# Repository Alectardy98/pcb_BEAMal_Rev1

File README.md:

# BEAMAL Rev. 1 
    A Custom Replacment PCB and case, using the IBM 6580 Displaywriter System as a base

All Supported Layouts can be seen [HERE](http://www.keyboard-layout-editor.com/#/gists/b96d65da63be744e5e54532b00e9445a)

xwhatsit/QMK atmega32u4 pcb for the IBM Model F XT and IBM Bigfoot

This version has NOT YET been tested, THIS IS A SMALL PRODUCTION OF 5 UNITS, NEVER TO BE SOLD AGAIN
- The firmware can be found in the firmware folder
- All files for production though JLCPCB can be found in the JLCPCB folder
- This pcb requires an xwhatsit to function, see [purdeaandrei's open source files](https://github.com/purdeaandrei/SMDModelFController)
- Note, even though this is a beamspring pcb, it will use a model F xWhatsit replacment controller
- Test Points are currently on the pcb, when building make sure to cover the bottom test points with eletrical tape to prevent a short
- The barrel Plate will need to be modified, A replacment barrel plate file will be provided with the custom case files

The PCB thickness should be 0.6mm or 0.08mm. This is thin enough to allow the board to flex into shape.
- 0.8mm tested and working

Standard glossy soldermask is probably the best choice. JLCPCB has had issues with wear on their black soldermask before. They have changed the formula, but a standard green/red/blue/yellow/purple/white/etc. glossy solder mask is probaby the safest bet for keyswitch wear resistance. Higher wear resistance might also be achieved by coating the front of the capacitive pads in silkscreen, as silkscreen is an extra layer of epoxy. I am unsure how this will affect keyfeel or actuation, however.

For connecting the board to an xwhatsit or other controller, I would recommend [3M 8132/06 100](https://www.digikey.com/en/products/detail/3m/8132-06-100/7809902), which has the correct pitch to connect this pcb to an xwhatsit

Capacitive pad footprints have been created spificly for this project, as the White whale beamspring has an off axis footprint aligment. In order to stay true to the origional desigen philosphy, that change has been made here also. Thank you to  All mesurements have beeen take from an origonal IBM Displaywrighter system (BAE). The key matrix of the PCB is custom, made by myself, guided purdeaandrei.

Released without warranty, use at your own risk.  
PRs & feedback welcome!

| Authors | 

Alectardy98

| Special Thanks |
   
purdeaandrei - For many things, this project would not have happened without him.

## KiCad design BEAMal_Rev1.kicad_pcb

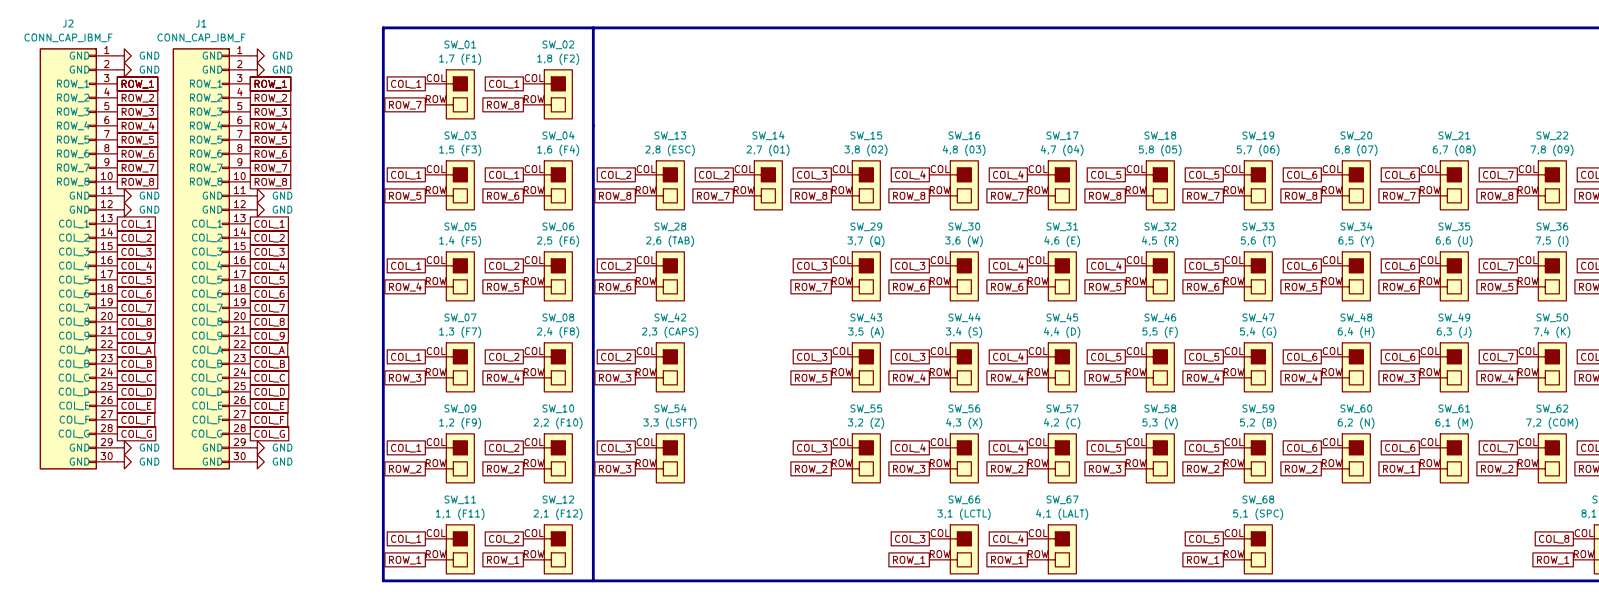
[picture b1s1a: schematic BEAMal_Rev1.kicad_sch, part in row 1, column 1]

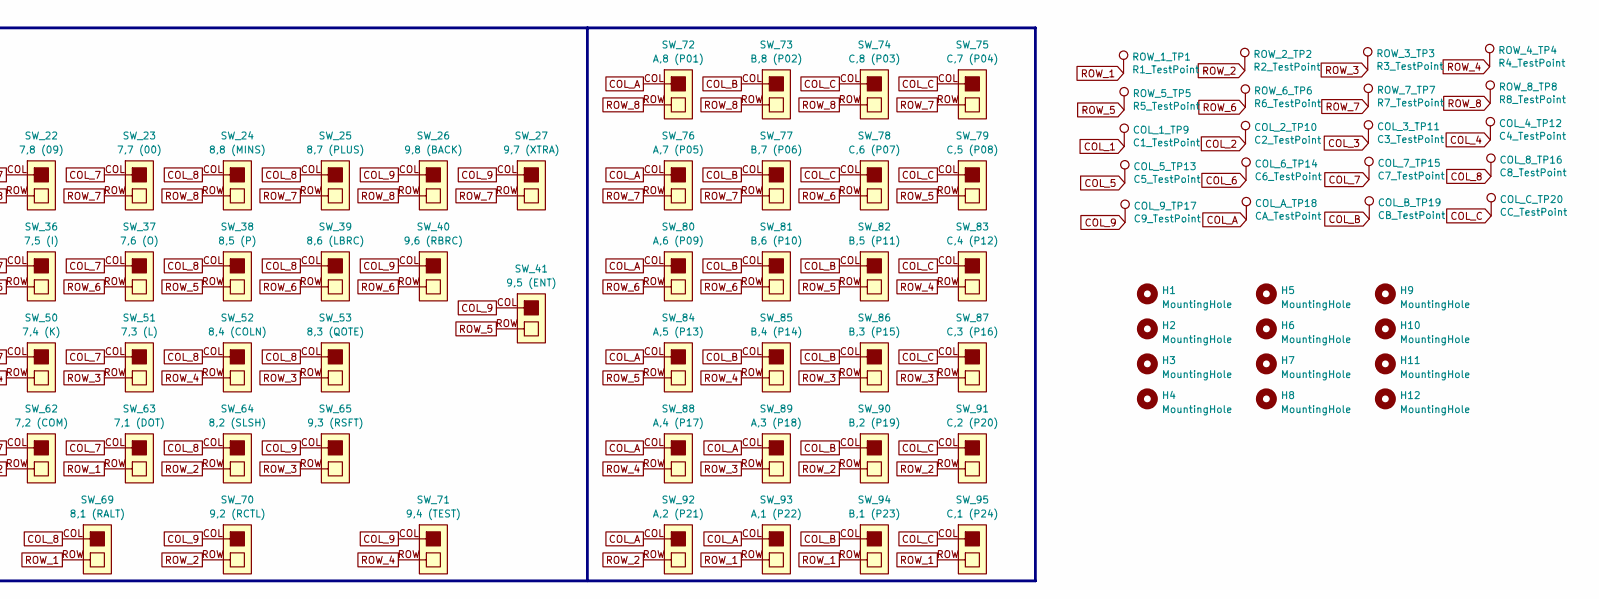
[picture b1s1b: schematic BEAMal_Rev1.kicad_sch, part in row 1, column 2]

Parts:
COL_1_TP9: C1_TestPoint; TestPoint_Pad_D1.0mm
COL_2_TP10: C2_TestPoint; TestPoint_Pad_D1.0mm
COL_3_TP11: C3_TestPoint; TestPoint_Pad_D1.0mm
COL_4_TP12: C4_TestPoint; TestPoint_Pad_D1.0mm
COL_5_TP13: C5_TestPoint; TestPoint_Pad_D1.0mm
COL_6_TP14: C6_TestPoint; TestPoint_Pad_D1.0mm
COL_7_TP15: C7_TestPoint; TestPoint_Pad_D1.0mm
COL_8_TP16: C8_TestPoint; TestPoint_Pad_D1.0mm
COL_9_TP17: C9_TestPoint; TestPoint_Pad_D1.0mm
COL_A_TP18: CA_TestPoint; TestPoint_Pad_D1.0mm
COL_B_TP19: CB_TestPoint; TestPoint_Pad_D1.0mm
COL_C_TP20: CC_TestPoint; TestPoint_Pad_D1.0mm
H1, H2, H3, H4, H5, H6, H7, H8, H9, H10, H11, H12: MountingHole; Generic-Mounthole_4.6mm
J1: CONN_CAP_IBM_F
J2: CONN_CAP_IBM_F; BEAMSPRING-CARD-EDGE
ROW_1_TP1: R1_TestPoint; TestPoint_Pad_D1.0mm
ROW_2_TP2: R2_TestPoint; TestPoint_Pad_D1.0mm
ROW_3_TP3: R3_TestPoint; TestPoint_Pad_D1.0mm
ROW_4_TP4: R4_TestPoint; TestPoint_Pad_D1.0mm
ROW_5_TP5: R5_TestPoint; TestPoint_Pad_D1.0mm
ROW_6_TP6: R6_TestPoint; TestPoint_Pad_D1.0mm
ROW_7_TP7: R7_TestPoint; TestPoint_Pad_D1.0mm
ROW_8_TP8: R8_TestPoint; TestPoint_Pad_D1.0mm
SW_01: 1,7 (F1); SW_CAP_IBM_B
SW_02: 1,8 (F2); SW_CAP_IBM_B
SW_03: 1,5 (F3); SW_CAP_IBM_B
SW_04: 1,6 (F4); SW_CAP_IBM_B
SW_05: 1,4 (F5); SW_CAP_IBM_B
SW_06: 2,5 (F6); SW_CAP_IBM_B
SW_07: 1,3 (F7); SW_CAP_IBM_B
SW_08: 2,4 (F8); SW_CAP_IBM_B
SW_09: 1,2 (F9); SW_CAP_IBM_B
SW_10: 2,2 (F10); SW_CAP_IBM_B
SW_11: 1,1 (F11); SW_CAP_IBM_B
SW_12: 2,1 (F12); SW_CAP_IBM_B
SW_13: 2,8 (ESC); SW_CAP_IBM_B
SW_14: 2,7 (01); SW_CAP_IBM_B
SW_15: 3,8 (02); SW_CAP_IBM_B
SW_16: 4,8 (03); SW_CAP_IBM_B
SW_17: 4,7 (04); SW_CAP_IBM_B
SW_18: 5,8 (05); SW_CAP_IBM_B
SW_19: 5,7 (06); SW_CAP_IBM_B
SW_20: 6,8 (07); SW_CAP_IBM_B
SW_21: 6,7 (08); SW_CAP_IBM_B
SW_22: 7,8 (09); SW_CAP_IBM_B
SW_23: 7,7 (00); SW_CAP_IBM_B
SW_24: 8,8 (MINS); SW_CAP_IBM_B
SW_25: 8,7 (PLUS); SW_CAP_IBM_B
SW_26: 9,8 (BACK); SW_CAP_IBM_B
SW_27: 9,7 (XTRA); SW_CAP_IBM_B
SW_28: 2,6 (TAB); SW_CAP_IBM_B
SW_29: 3,7 (Q); SW_CAP_IBM_B
SW_30: 3,6 (W); SW_CAP_IBM_B
SW_31: 4,6 (E); SW_CAP_IBM_B
SW_32: 4,5 (R); SW_CAP_IBM_B
SW_33: 5,6 (T); SW_CAP_IBM_B
SW_34: 6,5 (Y); SW_CAP_IBM_B
SW_35: 6,6 (U); SW_CAP_IBM_B
SW_36: 7,5 (I); SW_CAP_IBM_B
SW_37: 7,6 (O); SW_CAP_IBM_B
SW_38: 8,5 (P); SW_CAP_IBM_B
SW_39: 8,6 (LBRC); SW_CAP_IBM_B
SW_40: 9,6 (RBRC); SW_CAP_IBM_B
SW_41: 9,5 (ENT); SW_CAP_IBM_B
SW_42: 2,3 (CAPS); SW_CAP_IBM_B
SW_43: 3,5 (A); SW_CAP_IBM_B
SW_44: 3,4 (S); SW_CAP_IBM_B
SW_45: 4,4 (D); SW_CAP_IBM_B
SW_46: 5,5 (F); SW_CAP_IBM_B
SW_47: 5,4 (G); SW_CAP_IBM_B
SW_48: 6,4 (H); SW_CAP_IBM_B
SW_49: 6,3 (J); SW_CAP_IBM_B
SW_50: 7,4 (K); SW_CAP_IBM_B
SW_51: 7,3 (L); SW_CAP_IBM_B
SW_52: 8,4 (COLN); SW_CAP_IBM_B
SW_53: 8,3 (QOTE); SW_CAP_IBM_B
SW_54: 3,3 (LSFT); SW_CAP_IBM_B
SW_55: 3,2 (Z); SW_CAP_IBM_B
SW_56: 4,3 (X); SW_CAP_IBM_B
SW_57: 4,2 (C); SW_CAP_IBM_B
SW_58: 5,3 (V); SW_CAP_IBM_B
SW_59: 5,2 (B); SW_CAP_IBM_B
SW_60: 6,2 (N); SW_CAP_IBM_B
SW_61: 6,1 (M); SW_CAP_IBM_B
SW_62: 7,2 (COM); SW_CAP_IBM_B
SW_63: 7,1 (DOT); SW_CAP_IBM_B
SW_64: 8,2 (SLSH); SW_CAP_IBM_B
SW_65: 9,3 (RSFT); SW_CAP_IBM_B
SW_66: 3,1 (LCTL); SW_CAP_IBM_B
SW_67: 4,1 (LALT); SW_CAP_IBM_B
SW_68: 5,1 (SPC); SW_CAP_IBM_B
SW_69: 8,1 (RALT); SW_CAP_IBM_B
SW_70: 9,2 (RCTL); SW_CAP_IBM_B
SW_71: 9,4 (TEST); CAL_CAP_IBM_B
SW_72: A,8 (P01); SW_CAP_IBM_B
SW_73: B,8 (P02); SW_CAP_IBM_B
SW_74: C,8 (P03); SW_CAP_IBM_B
SW_75: C,7 (P04); SW_CAP_IBM_B
SW_76: A,7 (P05); SW_CAP_IBM_B
SW_77: B,7 (P06); SW_CAP_IBM_B
SW_78: C,6 (P07); SW_CAP_IBM_B
SW_79: C,5 (P08); SW_CAP_IBM_B
SW_80: A,6 (P09); SW_CAP_IBM_B
SW_81: B,6 (P10); SW_CAP_IBM_B
SW_82: B,5 (P11); SW_CAP_IBM_B
SW_83: C,4 (P12); SW_CAP_IBM_B
SW_84: A,5 (P13); SW_CAP_IBM_B
SW_85: B,4 (P14); SW_CAP_IBM_B
SW_86: B,3 (P15); SW_CAP_IBM_B
SW_87: C,3 (P16); SW_CAP_IBM_B
SW_88: A,4 (P17); SW_CAP_IBM_B
SW_89: A,3 (P18); SW_CAP_IBM_B
SW_90: B,2 (P19); SW_CAP_IBM_B
SW_91: C,2 (P20); SW_CAP_IBM_B
SW_92: A,2 (P21); SW_CAP_IBM_B
SW_93: A,1 (P22); SW_CAP_IBM_B
SW_94: B,1 (P23); SW_CAP_IBM_B
SW_95: C,1 (P24); SW_CAP_IBM_B

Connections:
COL_1: COL_1_TP9.1, J1.13 (COL_1), J2.13 (COL_1), SW_01.COL, SW_02.COL, SW_03.COL, SW_04.COL, SW_05.COL, SW_07.COL, SW_09.COL, SW_11.COL
COL_2: COL_2_TP10.1, J1.14 (COL_2), J2.14 (COL_2), SW_06.COL, SW_08.COL, SW_10.COL, SW_12.COL, SW_13.COL, SW_14.COL, SW_28.COL, SW_42.COL
COL_3: COL_3_TP11.1, J1.15 (COL_3), J2.15 (COL_3), SW_15.COL, SW_29.COL, SW_30.COL, SW_43.COL, SW_44.COL, SW_54.COL, SW_55.COL, SW_66.COL
COL_4: COL_4_TP12.1, J1.16 (COL_4), J2.16 (COL_4), SW_16.COL, SW_17.COL, SW_31.COL, SW_32.COL, SW_45.COL, SW_56.COL, SW_57.COL, SW_67.COL
COL_5: COL_5_TP13.1, J1.17 (COL_5), J2.17 (COL_5), SW_18.COL, SW_19.COL, SW_33.COL, SW_46.COL, SW_47.COL, SW_58.COL, SW_59.COL, SW_68.COL
COL_6: COL_6_TP14.1, J1.18 (COL_6), J2.18 (COL_6), SW_20.COL, SW_21.COL, SW_34.COL, SW_35.COL, SW_48.COL, SW_49.COL, SW_60.COL, SW_61.COL
COL_7: COL_7_TP15.1, J1.19 (COL_7), J2.19 (COL_7), SW_22.COL, SW_23.COL, SW_36.COL, SW_37.COL, SW_50.COL, SW_51.COL, SW_62.COL, SW_63.COL
COL_8: COL_8_TP16.1, J1.20 (COL_8), J2.20 (COL_8), SW_24.COL, SW_25.COL, SW_38.COL, SW_39.COL, SW_52.COL, SW_53.COL, SW_64.COL, SW_69.COL
COL_9: COL_9_TP17.1, J1.21 (COL_9), J2.21 (COL_9), SW_26.COL, SW_27.COL, SW_40.COL, SW_41.COL, SW_65.COL, SW_70.COL, SW_71.COL
COL_A: COL_A_TP18.1, J1.22 (COL_A), J2.22 (COL_A), SW_72.COL, SW_76.COL, SW_80.COL, SW_84.COL, SW_88.COL, SW_89.COL, SW_92.COL, SW_93.COL
COL_B: COL_B_TP19.1, J1.23 (COL_B), J2.23 (COL_B), SW_73.COL, SW_77.COL, SW_81.COL, SW_82.COL, SW_85.COL, SW_86.COL, SW_90.COL, SW_94.COL
COL_C: COL_C_TP20.1, J1.24 (COL_C), J2.24 (COL_C), SW_74.COL, SW_75.COL, SW_78.COL, SW_79.COL, SW_83.COL, SW_87.COL, SW_91.COL, SW_95.COL
COL_D: J1.25 (COL_D), J2.25 (COL_D)
COL_E: J1.26 (COL_E), J2.26 (COL_E)
COL_F: J1.27 (COL_F), J2.27 (COL_F)
COL_G: J1.28 (COL_G), J2.28 (COL_G)
GND: J1.1 (GND), J1.2 (GND), J1.11 (GND), J1.12 (GND), J1.29 (GND), J1.30 (GND), J2.1 (GND), J2.2 (GND), J2.11 (GND), J2.12 (GND), J2.29 (GND), J2.30 (GND)
ROW_1: J1.3 (ROW_1), J2.3 (ROW_1), ROW_1_TP1.1, SW_11.ROW, SW_12.ROW, SW_61.ROW, SW_63.ROW, SW_66.ROW, SW_67.ROW, SW_68.ROW, SW_69.ROW, SW_93.ROW, SW_94.ROW, SW_95.ROW
ROW_2: J1.4 (ROW_2), J2.4 (ROW_2), ROW_2_TP2.1, SW_09.ROW, SW_10.ROW, SW_55.ROW, SW_57.ROW, SW_59.ROW, SW_60.ROW, SW_62.ROW, SW_64.ROW, SW_70.ROW, SW_90.ROW, SW_91.ROW, SW_92.ROW
ROW_3: J1.5 (ROW_3), J2.5 (ROW_3), ROW_3_TP3.1, SW_07.ROW, SW_42.ROW, SW_49.ROW, SW_51.ROW, SW_53.ROW, SW_54.ROW, SW_56.ROW, SW_58.ROW, SW_65.ROW, SW_86.ROW, SW_87.ROW, SW_89.ROW
ROW_4: J1.6 (ROW_4), J2.6 (ROW_4), ROW_4_TP4.1, SW_05.ROW, SW_08.ROW, SW_44.ROW, SW_45.ROW, SW_47.ROW, SW_48.ROW, SW_50.ROW, SW_52.ROW, SW_71.ROW, SW_83.ROW, SW_85.ROW, SW_88.ROW
ROW_5: J1.7 (ROW_5), J2.7 (ROW_5), ROW_5_TP5.1, SW_03.ROW, SW_06.ROW, SW_32.ROW, SW_34.ROW, SW_36.ROW, SW_38.ROW, SW_41.ROW, SW_43.ROW, SW_46.ROW, SW_79.ROW, SW_82.ROW, SW_84.ROW
ROW_6: J1.8 (ROW_6), J2.8 (ROW_6), ROW_6_TP6.1, SW_04.ROW, SW_28.ROW, SW_30.ROW, SW_31.ROW, SW_33.ROW, SW_35.ROW, SW_37.ROW, SW_39.ROW, SW_40.ROW, SW_78.ROW, SW_80.ROW, SW_81.ROW
ROW_7: J1.9 (ROW_7), J2.9 (ROW_7), ROW_7_TP7.1, SW_01.ROW, SW_14.ROW, SW_17.ROW, SW_19.ROW, SW_21.ROW, SW_23.ROW, SW_25.ROW, SW_27.ROW, SW_29.ROW, SW_75.ROW, SW_76.ROW, SW_77.ROW
ROW_8: J1.10 (ROW_8), J2.10 (ROW_8), ROW_8_TP8.1, SW_02.ROW, SW_13.ROW, SW_15.ROW, SW_16.ROW, SW_18.ROW, SW_20.ROW, SW_22.ROW, SW_24.ROW, SW_26.ROW, SW_72.ROW, SW_73.ROW, SW_74.ROW

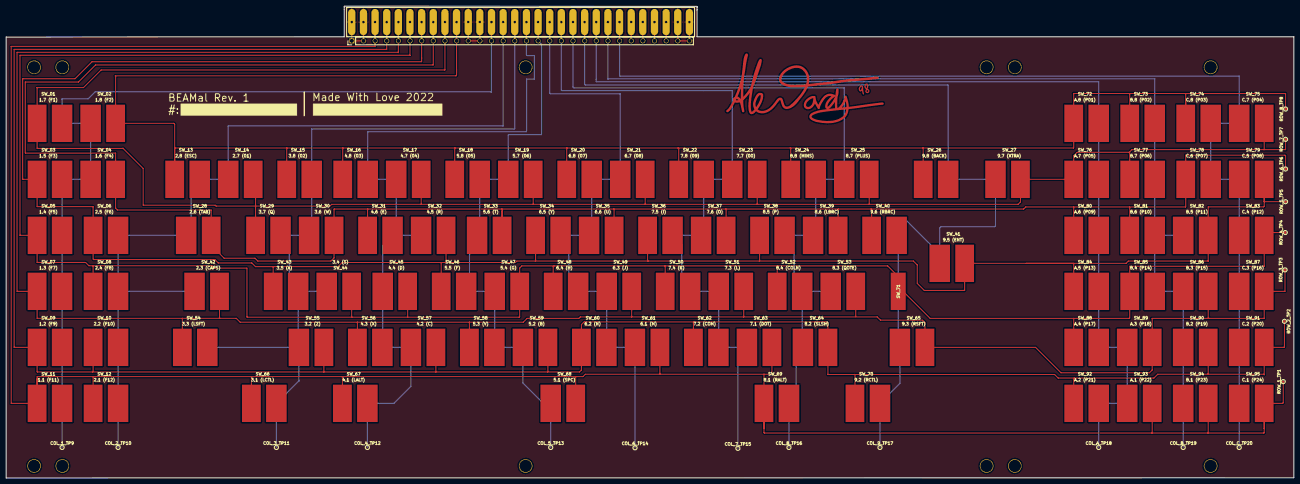
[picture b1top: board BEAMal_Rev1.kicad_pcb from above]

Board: 2 copper layers, 438.0 x 160.5 mm, 129 parts (0 on the bottom side), 25 nets.

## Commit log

2022-09-13 Rev 1
2022-09-13 Push
2022-09-13 Push Added Controller
2022-09-13 Push after changes #1
2022-09-13 update gerbers #1
2022-09-13 push save
2022-09-13 Fixes #2
    UPDATED gerbers
2022-09-13 push update #3
2022-09-13 puah
2022-09-13 psuh #4
2022-09-13 Update gerbers
2022-09-13 giving up on this
2022-09-13 Update and finish PCB
2022-09-13 MOVE README
2022-09-14 psuh
2022-10-17 pauh
2023-07-03 Clean up
